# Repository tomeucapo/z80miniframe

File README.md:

# Z80MiniFrame

Z80MiniFrame is a Z80-based microcomputer project. This repository contains its firmware source, hardware schematics and previously built firmware images.

## Hardware

The design includes:

- Z80 CPU
- 32 KiB ROM/EEPROM and 32 KiB RAM
- TMS9918 video display processor (VDP)
- AY-3-8910 programmable sound generator (PSG)
- Serial console
- PPI-based I/O and a keyboard interface

## Required tools
This project uses the ZMAC Z80 Macro assembler and LD80 linker from
http://48k.ca/zmac.html, as well as CMake.

## Build software
```
cmake -S . -B build
cmake --build build
```

This produces `build/bin/firmware.hex`. To program an EPROM, install `epromng`
and run `cmake --build build --target burn`.

The firmware system and EPROM programming settings can be changed at configure
time, for example with `-DFIRMWARE_SYSTEM=Z80AIO`,
`-DEPROM_MEMTYPE=27256`, and `-DEPROM_COM_PORT=COM6`.
The firmware build is configured for the `Z80AIO` target. In that configuration it also initializes the 8253 PIT. The source contains conditional code for other hardware configurations.

## Firmware

The firmware provides:

- A Z80 BASIC interpreter with VDP-aware console and graphics support
- A serial monitor for memory inspection, Intel HEX reception, execution at an address and keyboard testing
- VDP, PSG, keyboard, serial, cassette, PPI and PIT routines
- CompactFlash IDE PIO routines for 512-byte LBA28 sector reads and writes
- Interrupt-mode 2 support and firmware service routines at `RST $20`

The CompactFlash routines use the `$A0-$A7` I/O ports. Call `CF_INIT` before
transfers, then set the four-byte little-endian `CF_LBA` and two-byte
little-endian `CF_BUFFER` values and call `CF_READ_SECTOR` or
`CF_WRITE_SECTOR`. These routines provide raw sector access; they do not
implement a filesystem.

The FAT32 support validates a FAT32 superfloppy or a primary MBR partition
(`0x0B`/`0x0C`/`0x1B`/`0x1C`) and lists its root directory in BASIC with `FILES`. The BASIC
statement invokes the directory routine through the firmware `RST $20`
service dispatcher. Names are displayed in 8.3 format; file read/write
operations are not implemented yet. Monitor command `F` initializes the CF
and mounts the volume. In BASIC, enter `FILES` to initialize, mount and list
the root directory.

At startup, the monitor offers these commands:

| Key | Function |
| --- | --- |
| `B` | Start BASIC |
| `M` | Dump memory |
| `R` | Receive Intel HEX records |
| `G` | Jump to an address |
| `T` | Run the keyboard test |
| `C` | Initialize the CompactFlash card |
| `F` | Initialize the CF and mount a FAT32 volume |
| `L` | Initialize the CF and list the FAT32 root directory |
| `?` | Show help |

Monitor command `R` receives Intel HEX over the UART. It validates each
record checksum, accepts data, EOF, extended-segment and extended-linear
records within the 16-bit Z80 address space, and ignores start-address
records. Data is written only to free RAM (`TEMPSTACK+1` through `$FDFF` in
the current memory map); the upper 512 bytes are reserved for the FAT32
sector buffer.

## Repository layout

| Path | Contents |
| --- | --- |
| `source/` | Assembly source, includes, Makefile and tests |
| `source/include/` | Hardware and firmware definitions |
| `source/tests/` | Assembly and BASIC test programs |
| `source/bin/` | Build output (`firmware.hex`, linker symbols and intermediate files) |
| `firmware/` | Checked-in firmware images from earlier releases |
| `schematics/` | Hardware schematics, PCB files and component libraries |

## Programming the ROM

The Makefile has a `burn` target that invokes `epromng`. Its defaults are `MEMTYPE=27256` and `COMEPROM=COM6`; change these in `source/Makefile` to match your programmer and port before using the target. You can also program `source/bin/firmware.hex` with a compatible programmer configured for the ROM fitted to your board.

## Hardware documentation

PDF schematics are available in `schematics/`, including `CPU_IO_Board.pdf`, `VDP.pdf`, `PSG.pdf` and `SIO_PIO.pdf`. The KiCad project for the Z80 All-in-One board is in `schematics/Z80Allinone/Z80AllInOne/`.

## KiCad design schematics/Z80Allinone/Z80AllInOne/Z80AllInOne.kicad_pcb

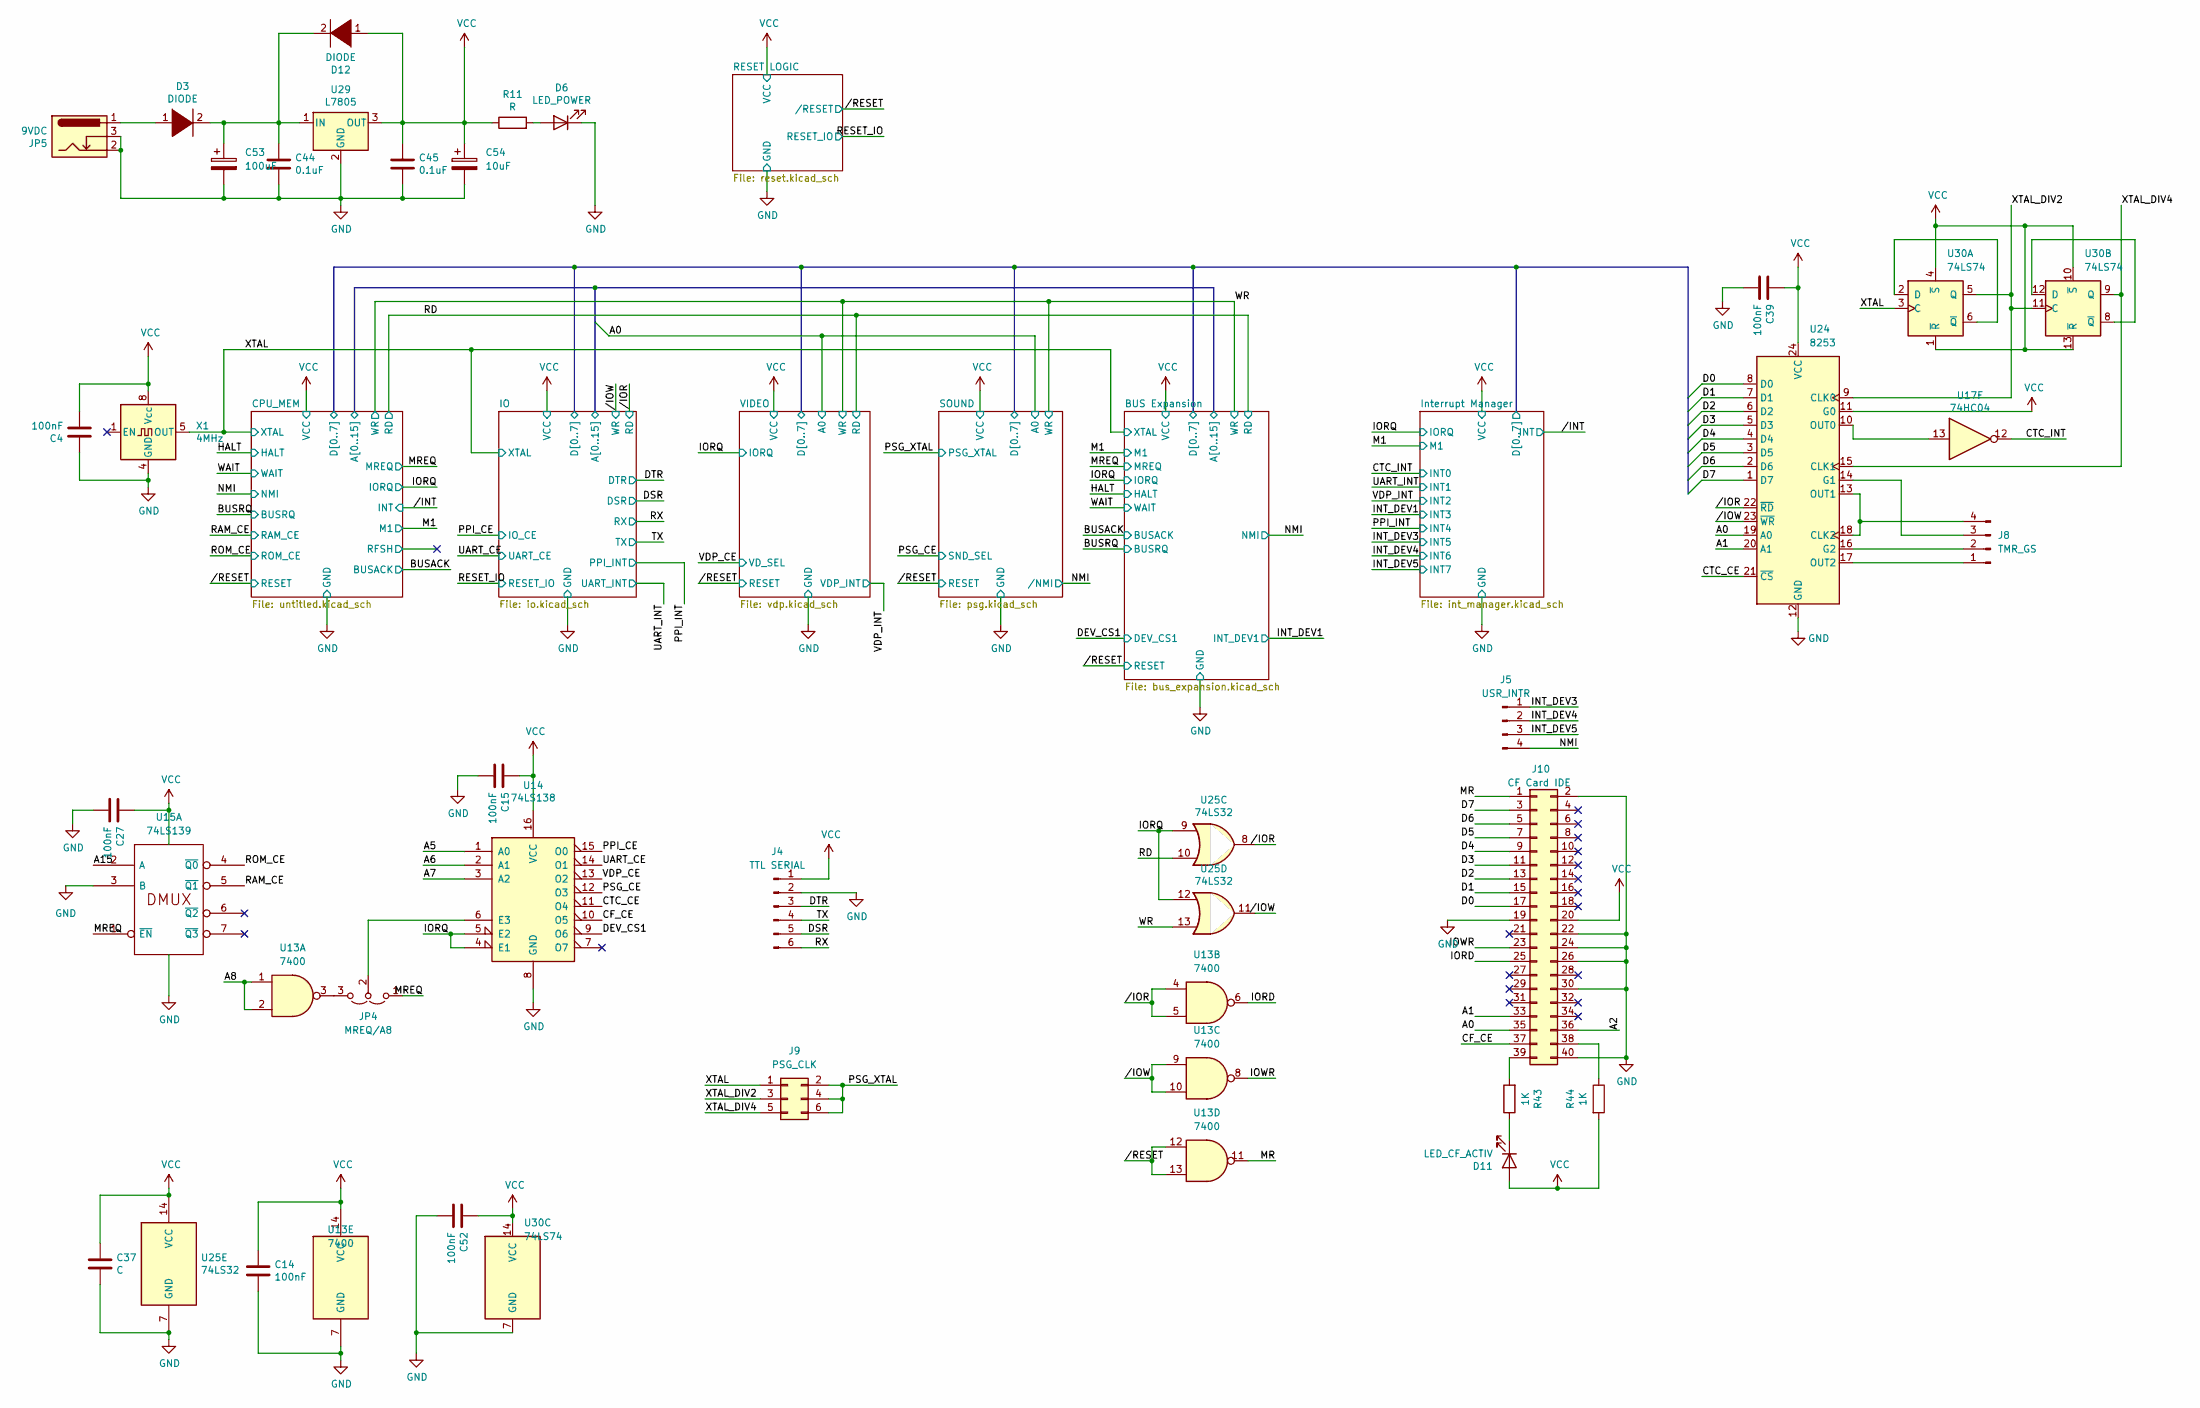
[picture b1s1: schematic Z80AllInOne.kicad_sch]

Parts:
C4, C14, C15, C27, C39, C52: 100nF; C_Disc_D7.0mm_W2.5mm_P5.00mm
C37: C; C_Disc_D7.0mm_W2.5mm_P5.00mm
C44, C45: 0.1uF; C_Radial_D6.3mm_H5.0mm_P2.50mm
C53: 100uF; CP_Radial_D8.0mm_P3.80mm
C54: 10uF; CP_Radial_D8.0mm_P3.80mm
D3, D12: DIODE; D_A-405_P7.62mm_Horizontal
D6: LED_POWER; LED_D3.0mm
D11: LED_CF_ACTIV; LED_D3.0mm
J4: TTL SERIAL; PinHeader_1x06_P2.54mm_Vertical
J5: USR_INTR; PinHeader_1x04_P2.54mm_Vertical
J8: TMR_GS; PinHeader_1x04_P2.54mm_Vertical
J9: PSG_CLK; PinHeader_2x03_P2.54mm_Vertical
J10: CF Card IDE; IDC-Header_2x20_P2.54mm_Vertical
JP4: MREQ/A8; PinHeader_1x03_P2.54mm_Vertical
JP5: 9VDC; BarrelJack_Wuerth_6941xx301002
R11: R; R_Axial_DIN0207_L6.3mm_D2.5mm_P10.16mm_Horizontal
R43, R44: 1K; R_Axial_DIN0207_L6.3mm_D2.5mm_P10.16mm_Horizontal
U13: 7400; DIP-14_W7.62mm_LongPads
U14: 74LS138; DIP-16_W7.62mm_LongPads
U15: 74LS139; DIP-16_W7.62mm_Socket
U17: 74HC04; DIP-14_W7.62mm_Socket_LongPads
U24: 8253; DIP-24_W15.24mm
U25: 74LS32; DIP-14_W7.62mm_LongPads
U29: L7805; TO-220-3_Horizontal_TabDown
U30: 74LS74; DIP-14_W7.62mm_LongPads
X1: 4MHz; Oscillator_DIP-8

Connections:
/BUS Expansion/D0: J10.17, U24.8 (D0); also elsewhere on the board
/BUS Expansion/D1: J10.15, U24.7 (D1); also elsewhere on the board
/BUS Expansion/D2: J10.13, U24.6 (D2); also elsewhere on the board
/BUS Expansion/D3: J10.11, U24.5 (D3); also elsewhere on the board
/BUS Expansion/D4: J10.9, U24.4 (D4); also elsewhere on the board
/BUS Expansion/D5: J10.7, U24.3 (D5); also elsewhere on the board
/BUS Expansion/D6: J10.5, U24.2 (D6); also elsewhere on the board
/BUS Expansion/D7: J10.3, U24.1 (D7); also elsewhere on the board
/CF_CE: J10.37, U14.10 (O5)
/CTC_CE: U14.11 (O4), U24.21 (~CS)
/CTC_INT: U17.12; also elsewhere on the board
/DEV_CS1: U14.9 (O6); also elsewhere on the board
/DSR: J4.5; also elsewhere on the board
/DTR: J4.3; also elsewhere on the board
/INT_DEV3: J5.1; also elsewhere on the board
/INT_DEV4: J5.2; also elsewhere on the board
/INT_DEV5: J5.3; also elsewhere on the board
/IO/A0: J10.35, U24.19 (A0); also elsewhere on the board
/IO/A1: J10.33, U24.20 (A1); also elsewhere on the board
/IO/A2: J10.36; also elsewhere on the board
/IO/A5: U14.1 (A0); also elsewhere on the board
/IO/A6: U14.2 (A1); also elsewhere on the board
/IO/A7: U14.3 (A2); also elsewhere on the board
/IO/A8: U13.1, U13.2; also elsewhere on the board
/IO/A15: U15.2 (A); also elsewhere on the board
/IORD: J10.25, U13.6
/IORQ: U14.4 (E1), U14.5 (E2), U25.9, U25.12; also elsewhere on the board
/IOWR: J10.23, U13.8
/MR: J10.1, U13.11
/MREQ: JP4.1 (A), U15.1 (~EN); also elsewhere on the board
/NMI: J5.4; also elsewhere on the board
/PPI_CE: U14.15 (O0); also elsewhere on the board
/PSG_CE: U14.12 (O3); also elsewhere on the board
/PSG_XTAL: J9.2, J9.4, J9.6; also elsewhere on the board
/RAM_CE: U15.5 (~Q1); also elsewhere on the board
/RD: U25.10; also elsewhere on the board
/ROM_CE: U15.4 (~Q0); also elsewhere on the board
/RX: J4.6; also elsewhere on the board
/TX: J4.4; also elsewhere on the board
/UART_CE: U14.14 (O1); also elsewhere on the board
/VDP_CE: U14.13 (O2); also elsewhere on the board
/WR: U25.13; also elsewhere on the board
/XTAL: J9.1, U30.3 (C), X1.5 (OUT); also elsewhere on the board
/XTAL_DIV2: J9.3, U24.9 (CLK0), U30.5 (Q), U30.11 (C)
/XTAL_DIV4: J9.5, U24.15 (CLK1), U30.9 (Q)
//IOR: U13.4, U13.5, U24.22 (~RD), U25.8; also elsewhere on the board
//IOW: U13.9, U13.10, U24.23 (~WR), U25.11; also elsewhere on the board
//RESET: U13.12, U13.13; also elsewhere on the board
GND: C4.1, C14.2, C15.2, C27.2, C37.1, C39.2, C44.2, C45.2, C52.2, C53.2, C54.2, D6.1 (K), J4.2, J10.2, J10.19, J10.22, J10.24, J10.26, J10.30, J10.40, JP5.2, JP5.3, U13.7 (GND), U14.8 (GND), U15.3 (B), U15.8 (GND), U24.12 (GND), U25.7 (GND), U29.2 (GND), U30.7 (GND), X1.4 (GND); also elsewhere on the board
unnamed: D3.1 (K), JP5.1
unnamed: D6.2 (A), R11.2
unnamed: D11.1 (K), R43.1
unnamed: C44.1, C53.1, D3.2 (A), D12.2 (A), U29.1 (IN)
unnamed: J8.1, U24.17 (OUT2)
unnamed: J8.2, U24.16 (G2)
unnamed: J8.3, U24.14 (G1)
unnamed: J8.4, U24.13 (OUT1), U24.18 (CLK2)
unnamed: J10.38, R44.1
unnamed: J10.39, R43.2
unnamed: JP4.3 (B), U13.3
unnamed: JP4.2 (C), U14.6 (E3)
unnamed: U17.13, U24.10 (OUT0)
unnamed: U30.2 (D), U30.6 (~Q)
unnamed: U30.8 (~Q), U30.12 (D)
VCC: C4.2, C14.1, C15.1, C27.1, C37.2, C39.1, C45.1, C52.1, C54.1, D11.2 (A), D12.1 (K), J4.1, J10.20, R11.1, R44.2, U13.14 (VCC), U14.16 (VCC), U15.16 (VCC), U24.11 (G0), U24.24 (VCC), U25.14 (VCC), U29.3 (OUT), U30.1 (~R), U30.4 (~S), U30.10 (~S), U30.13 (~R), U30.14 (VCC), X1.8 (Vcc); also elsewhere on the board

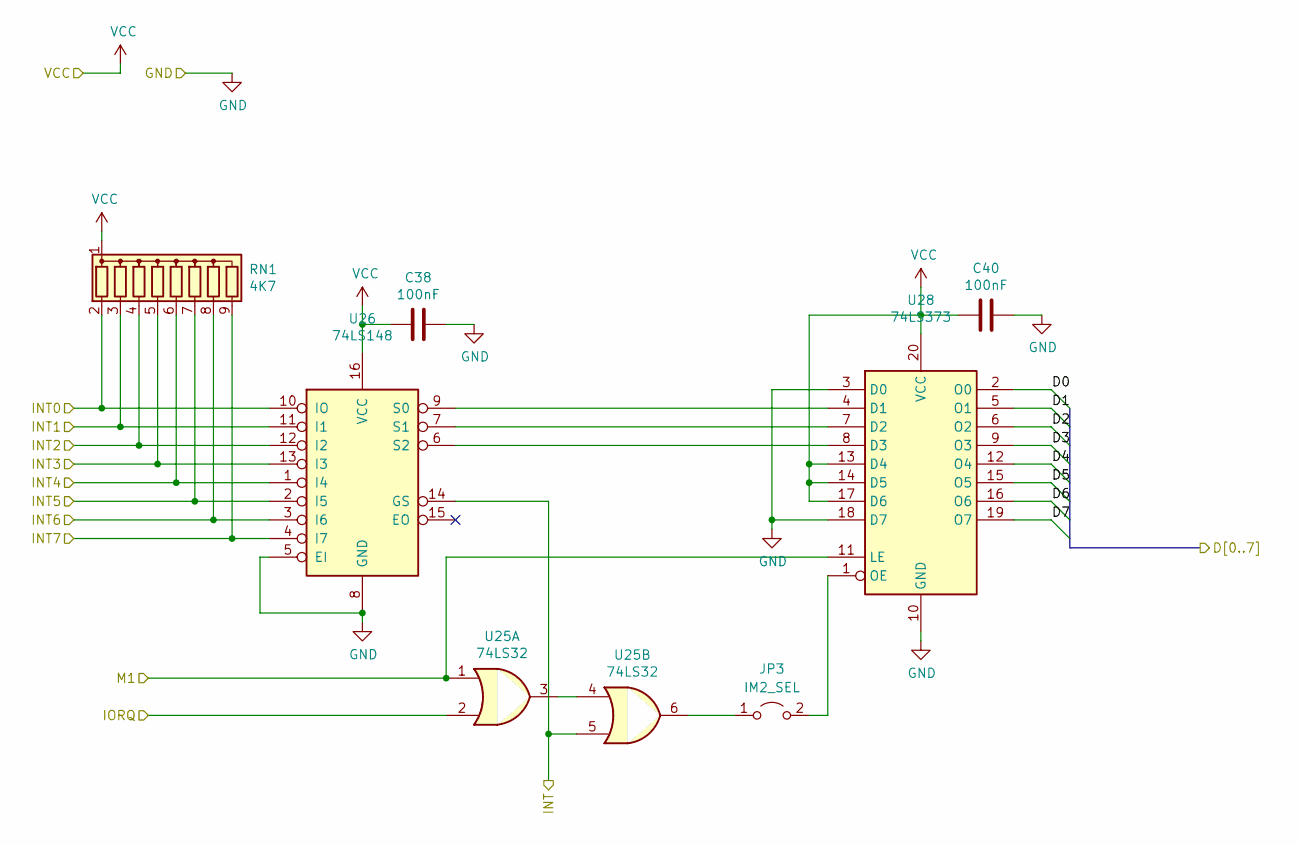
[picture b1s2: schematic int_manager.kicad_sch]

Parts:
C38, C40: 100nF; C_Disc_D7.0mm_W2.5mm_P5.00mm
JP3: IM2_SEL; PinHeader_1x02_P2.54mm_Vertical
RN1: 4K7; R_Array_SIP9
U25: 74LS32; DIP-14_W7.62mm_LongPads
U26: 74LS148; DIP-16_W7.62mm_LongPads
U28: 74LS373; DIP-20_W7.62mm_LongPads

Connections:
/BUS Expansion/D0: U28.2 (O0); also elsewhere on the board
/BUS Expansion/D1: U28.5 (O1); also elsewhere on the board
/BUS Expansion/D2: U28.6 (O2); also elsewhere on the board
/BUS Expansion/D3: U28.9 (O3); also elsewhere on the board
/BUS Expansion/D4: U28.12 (O4); also elsewhere on the board
/BUS Expansion/D5: U28.15 (O5); also elsewhere on the board
/BUS Expansion/D6: U28.16 (O6); also elsewhere on the board
/BUS Expansion/D7: U28.19 (O7); also elsewhere on the board
/CTC_INT: RN1.2 (R1), U26.10 (IO); also elsewhere on the board
/INT_DEV1: RN1.5 (R4), U26.13 (I3); also elsewhere on the board
/INT_DEV3: RN1.7 (R6), U26.2 (I5); also elsewhere on the board
/INT_DEV4: RN1.8 (R7), U26.3 (I6); also elsewhere on the board
/INT_DEV5: RN1.9 (R8), U26.4 (I7); also elsewhere on the board
/IORQ: U25.2; also elsewhere on the board
/M1: U25.1, U28.11 (LE); also elsewhere on the board
/PPI_INT: RN1.6 (R5), U26.1 (I4); also elsewhere on the board
/UART_INT: RN1.3 (R2), U26.11 (I1); also elsewhere on the board
/VDP_INT: RN1.4 (R3), U26.12 (I2); also elsewhere on the board
//INT: U25.5, U26.14 (GS); also elsewhere on the board
GND: C38.2, C40.2, U26.5 (EI), U26.8 (GND), U28.3 (D0), U28.10 (GND), U28.18 (D7); also elsewhere on the board
unnamed: JP3.1 (A), U25.6
unnamed: JP3.2 (B), U28.1 (OE)
unnamed: U25.3, U25.4
unnamed: U26.9 (S0), U28.4 (D1)
unnamed: U26.7 (S1), U28.7 (D2)
unnamed: U26.6 (S2), U28.8 (D3)
VCC: C38.1, C40.1, RN1.1 (common), U26.16 (VCC), U28.13 (D4), U28.14 (D5), U28.17 (D6), U28.20 (VCC); also elsewhere on the board

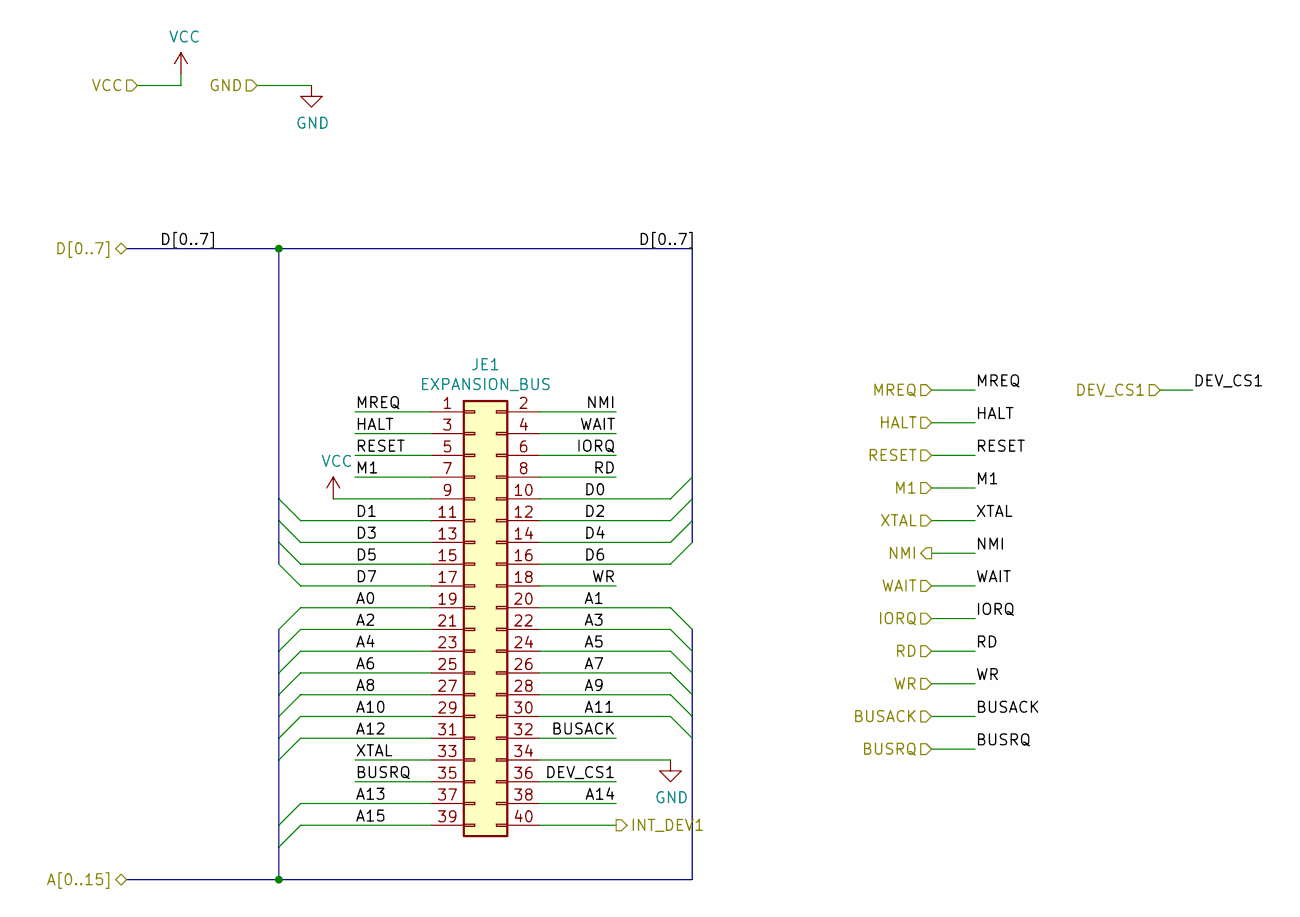
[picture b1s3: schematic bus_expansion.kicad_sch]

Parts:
JE1: EXPANSION_BUS; EdgeConector_40pin

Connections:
/BUS Expansion/D0: JE1.10; also elsewhere on the board
/BUS Expansion/D1: JE1.11; also elsewhere on the board
/BUS Expansion/D2: JE1.12; also elsewhere on the board
/BUS Expansion/D3: JE1.13; also elsewhere on the board
/BUS Expansion/D4: JE1.14; also elsewhere on the board
/BUS Expansion/D5: JE1.15; also elsewhere on the board
/BUS Expansion/D6: JE1.16; also elsewhere on the board
/BUS Expansion/D7: JE1.17; also elsewhere on the board
/BUSACK: JE1.32; also elsewhere on the board
/BUSRQ: JE1.35; also elsewhere on the board
/DEV_CS1: JE1.36; also elsewhere on the board
/HALT: JE1.3; also elsewhere on the board
/INT_DEV1: JE1.40; also elsewhere on the board
/IO/A0: JE1.19; also elsewhere on the board
/IO/A1: JE1.20; also elsewhere on the board
/IO/A2: JE1.21; also elsewhere on the board
/IO/A3: JE1.22; also elsewhere on the board
/IO/A4: JE1.23; also elsewhere on the board
/IO/A5: JE1.24; also elsewhere on the board
/IO/A6: JE1.25; also elsewhere on the board
/IO/A7: JE1.26; also elsewhere on the board
/IO/A8: JE1.27; also elsewhere on the board
/IO/A9: JE1.28; also elsewhere on the board
/IO/A10: JE1.29; also elsewhere on the board
/IO/A11: JE1.30; also elsewhere on the board
/IO/A12: JE1.31; also elsewhere on the board
/IO/A13: JE1.37; also elsewhere on the board
/IO/A14: JE1.38; also elsewhere on the board
/IO/A15: JE1.39; also elsewhere on the board
/IORQ: JE1.6; also elsewhere on the board
/M1: JE1.7; also elsewhere on the board
/MREQ: JE1.1; also elsewhere on the board
/NMI: JE1.2; also elsewhere on the board
/RD: JE1.8; also elsewhere on the board
/WAIT: JE1.4; also elsewhere on the board
/WR: JE1.18; also elsewhere on the board
/XTAL: JE1.33; also elsewhere on the board
//RESET: JE1.5; also elsewhere on the board
GND: JE1.34; also elsewhere on the board
VCC: JE1.9; also elsewhere on the board

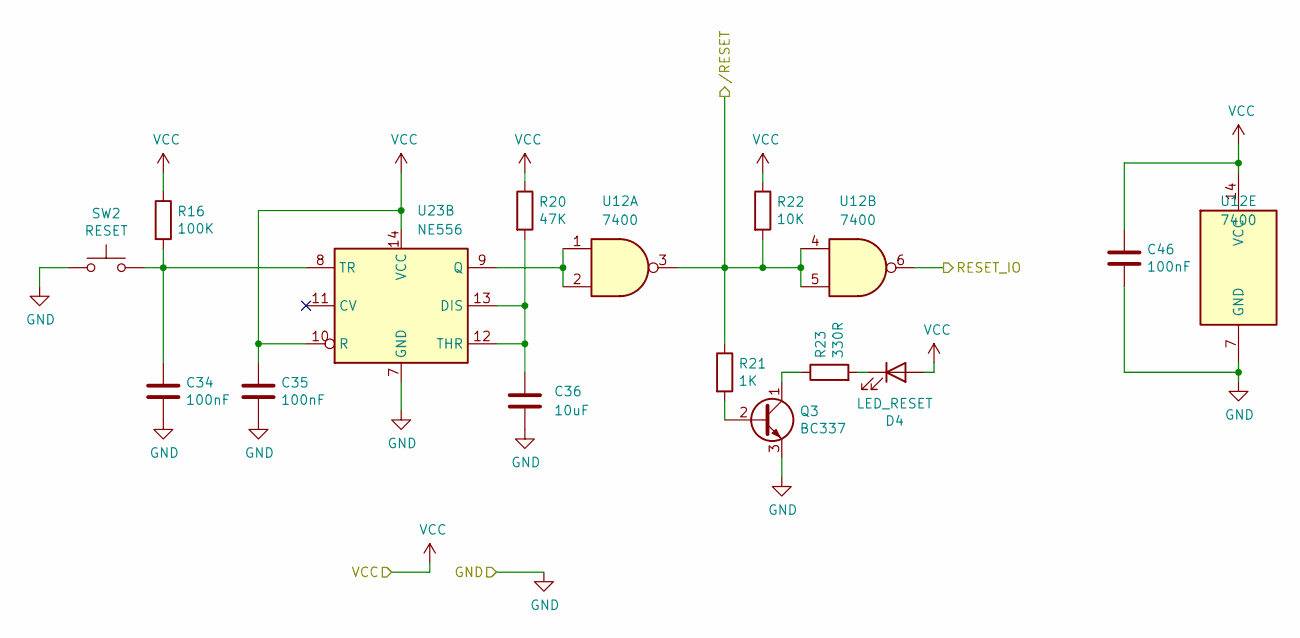
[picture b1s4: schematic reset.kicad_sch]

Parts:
C34, C35, C46: 100nF; C_Disc_D7.0mm_W2.5mm_P5.00mm
C36: 10uF; CP_Radial_D5.0mm_P2.50mm
D4: LED_RESET; LED_D3.0mm
Q3: BC337; TO-92_Inline
R16: 100K; R_Axial_DIN0207_L6.3mm_D2.5mm_P7.62mm_Horizontal
R20: 47K; R_Axial_DIN0207_L6.3mm_D2.5mm_P7.62mm_Horizontal
R21: 1K; R_Axial_DIN0207_L6.3mm_D2.5mm_P7.62mm_Horizontal
R22: 10K; R_Axial_DIN0207_L6.3mm_D2.5mm_P7.62mm_Horizontal
R23: 330R; R_Axial_DIN0207_L6.3mm_D2.5mm_P7.62mm_Horizontal
SW2: RESET; SW_PUSH_6mm_H5mm
U12: 7400; DIP-14_W7.62mm_LongPads
U23: NE556; DIP-14_W7.62mm_LongPads

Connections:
/RESET_IO: U12.6; also elsewhere on the board
//RESET: R21.1, R22.2, U12.3, U12.4, U12.5; also elsewhere on the board
GND: C34.2, C35.2, C36.2, C46.2, Q3.3 (E), SW2.1, U12.7 (GND), U23.7 (GND); also elsewhere on the board
unnamed: D4.1 (K), R23.2
unnamed: Q3.2 (B), R21.2
unnamed: Q3.1 (C), R23.1
unnamed: C36.1, R20.2, U23.12 (THR), U23.13 (DIS)
unnamed: U12.1, U12.2, U23.9 (Q)
unnamed: C34.1, R16.2, SW2.2, U23.8 (TR)
VCC: C35.1, C46.1, D4.2 (A), R16.1, R20.1, R22.1, U12.14 (VCC), U23.10 (R), U23.14 (VCC); also elsewhere on the board

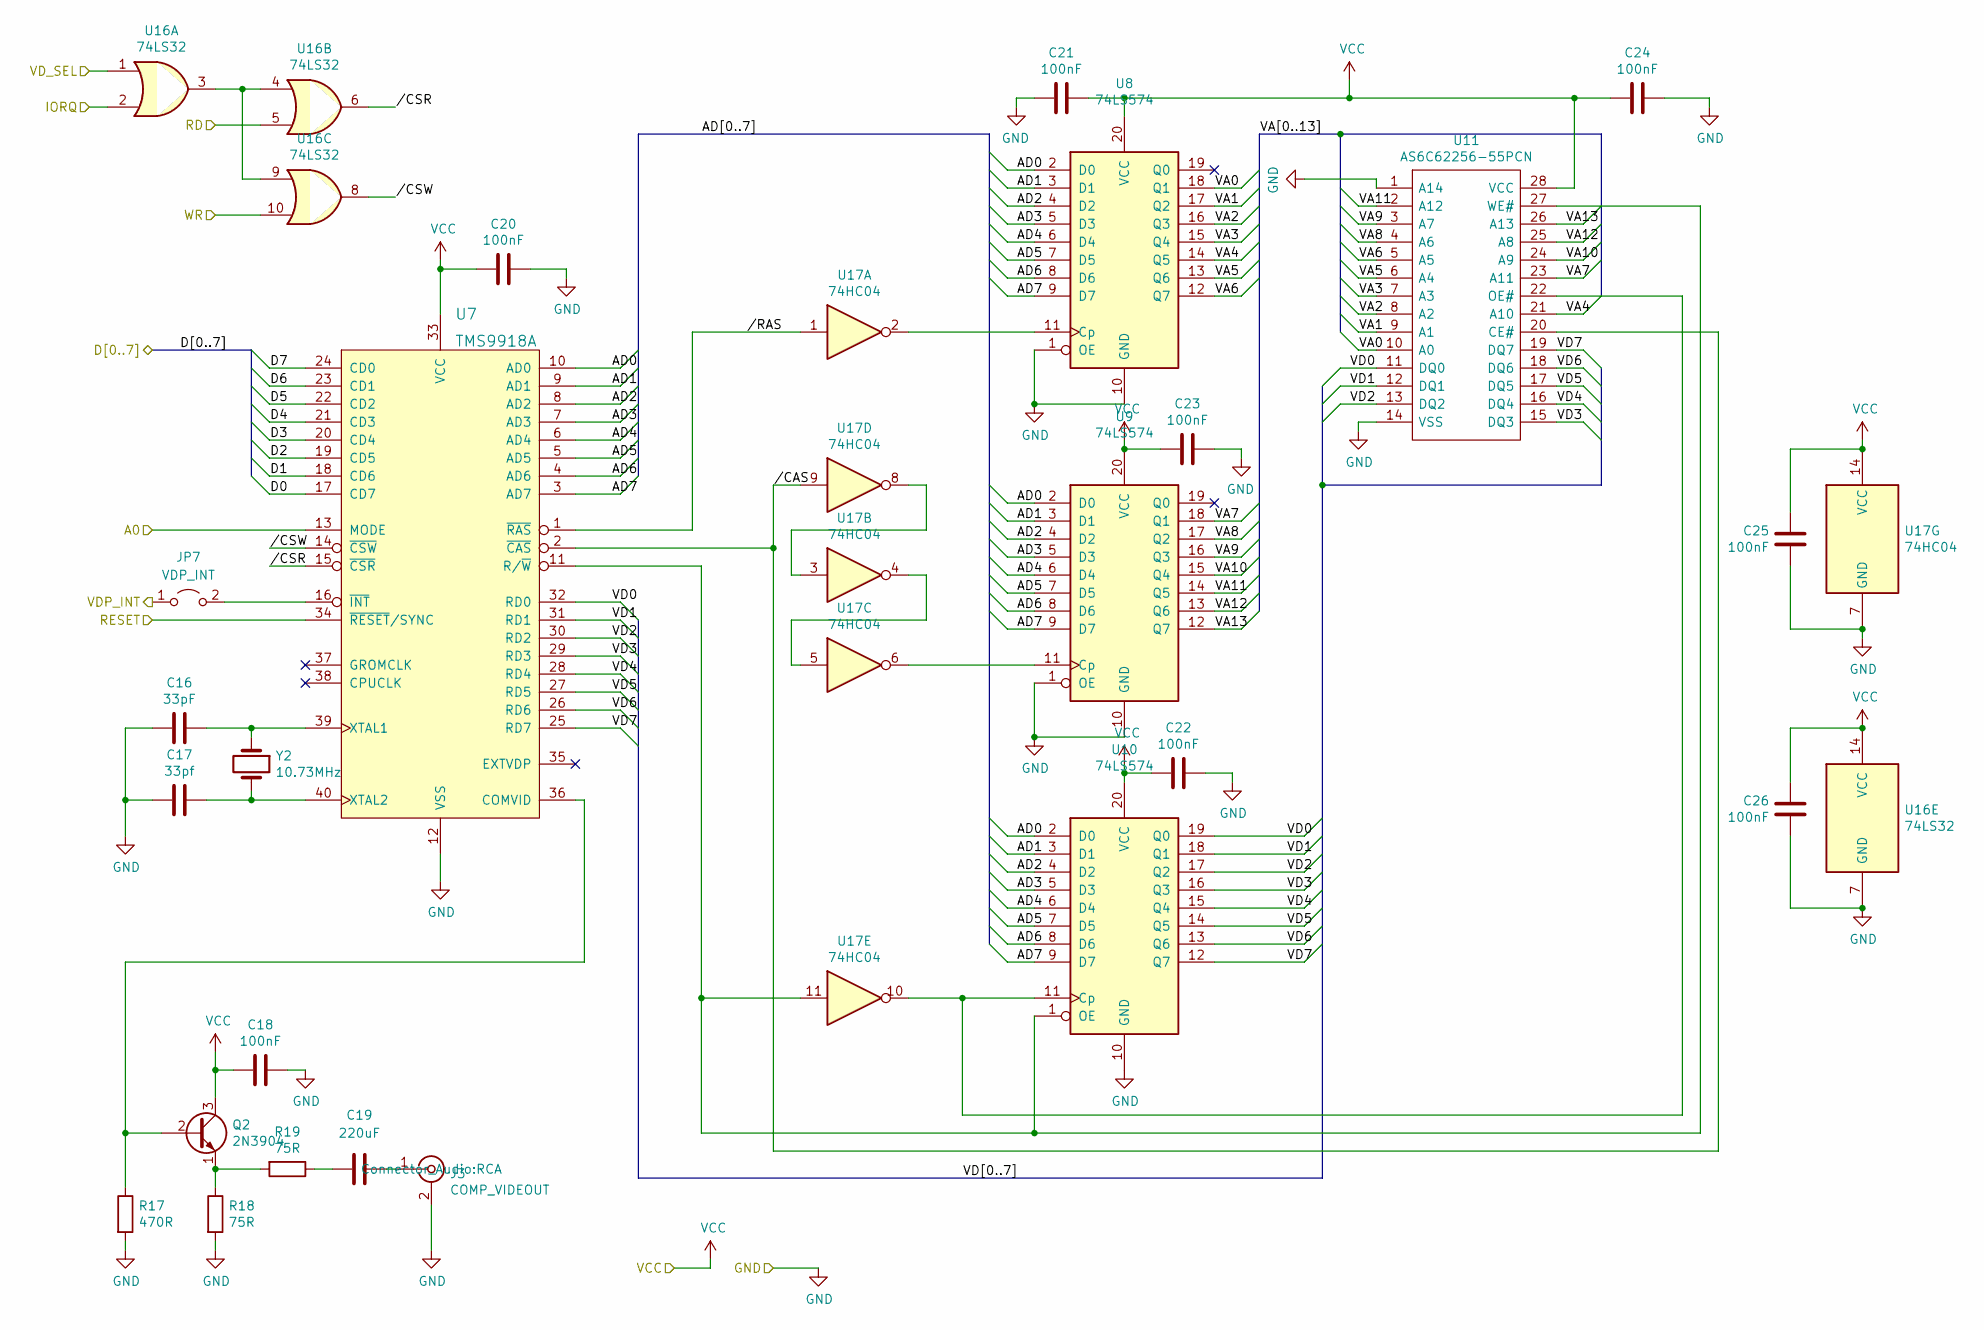
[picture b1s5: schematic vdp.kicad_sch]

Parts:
C16: 33pF; C_Disc_D7.0mm_W2.5mm_P5.00mm
C17: 33pf; C_Disc_D7.0mm_W2.5mm_P5.00mm
C18, C20, C21, C22, C23, C24, C25, C26: 100nF; C_Disc_D7.0mm_W2.5mm_P5.00mm
C19: 220uF; CP_Radial_Tantal_D6.0mm_P2.50mm
J3: COMP_VIDEOUT; RCA
JP7: VDP_INT; PinHeader_1x02_P2.54mm_Vertical
Q2: 2N3904; TO-92_Inline
R17: 470R; R_Axial_DIN0207_L6.3mm_D2.5mm_P10.16mm_Horizontal
R18, R19: 75R; R_Axial_DIN0207_L6.3mm_D2.5mm_P10.16mm_Horizontal
U7: TMS9918A; DIP-40_W15.24mm_LongPads
U8, U9, U10: 74LS574; DIP-20_W7.62mm_Socket_LongPads
U11: AS6C62256-55PCN; DIP-28_W15.24mm_LongPads; Manufacturer_Part_Number AS6C62256-55PCN; Mouser Part Number 913-AS6C62256-55PCN
U16: 74LS32; DIP-14_W7.62mm_LongPads
U17: 74HC04; DIP-14_W7.62mm_Socket_LongPads
Y2: 10.73MHz; Crystal_HC18-U_Vertical

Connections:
/BUS Expansion/D0: U7.17 (CD7); also elsewhere on the board
/BUS Expansion/D1: U7.18 (CD6); also elsewhere on the board
/BUS Expansion/D2: U7.19 (CD5); also elsewhere on the board
/BUS Expansion/D3: U7.20 (CD4); also elsewhere on the board
/BUS Expansion/D4: U7.21 (CD3); also elsewhere on the board
/BUS Expansion/D5: U7.22 (CD2); also elsewhere on the board
/BUS Expansion/D6: U7.23 (CD1); also elsewhere on the board
/BUS Expansion/D7: U7.24 (CD0); also elsewhere on the board
/IO/A0: U7.13 (MODE); also elsewhere on the board
/IORQ: U16.2; also elsewhere on the board
/RD: U16.5; also elsewhere on the board
/VDP_CE: U16.1; also elsewhere on the board
/VDP_INT: JP7.1 (A); also elsewhere on the board
/VIDEO/AD0: U7.10 (AD0), U8.2 (D0), U9.2 (D0), U10.2 (D0)
/VIDEO/AD1: U7.9 (AD1), U8.3 (D1), U9.3 (D1), U10.3 (D1)
/VIDEO/AD2: U7.8 (AD2), U8.4 (D2), U9.4 (D2), U10.4 (D2)
/VIDEO/AD3: U7.7 (AD3), U8.5 (D3), U9.5 (D3), U10.5 (D3)
/VIDEO/AD4: U7.6 (AD4), U8.6 (D4), U9.6 (D4), U10.6 (D4)
/VIDEO/AD5: U7.5 (AD5), U8.7 (D5), U9.7 (D5), U10.7 (D5)
/VIDEO/AD6: U7.4 (AD6), U8.8 (D6), U9.8 (D6), U10.8 (D6)
/VIDEO/AD7: U7.3 (AD7), U8.9 (D7), U9.9 (D7), U10.9 (D7)
/VIDEO/VA0: U8.18 (Q1), U11.10 (A0)
/VIDEO/VA1: U8.17 (Q2), U11.9 (A1)
/VIDEO/VA2: U8.16 (Q3), U11.8 (A2)
/VIDEO/VA3: U8.15 (Q4), U11.7 (A3)
/VIDEO/VA4: U8.14 (Q5), U11.21 (A10)
/VIDEO/VA5: U8.13 (Q6), U11.6 (A4)
/VIDEO/VA6: U8.12 (Q7), U11.5 (A5)
/VIDEO/VA7: U9.18 (Q1), U11.23 (A11)
/VIDEO/VA8: U9.17 (Q2), U11.4 (A6)
/VIDEO/VA9: U9.16 (Q3), U11.3 (A7)
/VIDEO/VA10: U9.15 (Q4), U11.24 (A9)
/VIDEO/VA11: U9.14 (Q5), U11.2 (A12)
/VIDEO/VA12: U9.13 (Q6), U11.25 (A8)
/VIDEO/VA13: U9.12 (Q7), U11.26 (A13)
/VIDEO/VD0: U7.32 (RD0), U10.19 (Q0), U11.11 (DQ0)
/VIDEO/VD1: U7.31 (RD1), U10.18 (Q1), U11.12 (DQ1)
/VIDEO/VD2: U7.30 (RD2), U10.17 (Q2), U11.13 (DQ2)
/VIDEO/VD3: U7.29 (RD3), U10.16 (Q3), U11.15 (DQ3)
/VIDEO/VD4: U7.28 (RD4), U10.15 (Q4), U11.16 (DQ4)
/VIDEO/VD5: U7.27 (RD5), U10.14 (Q5), U11.17 (DQ5)
/VIDEO/VD6: U7.26 (RD6), U10.13 (Q6), U11.18 (DQ6)
/VIDEO/VD7: U7.25 (RD7), U10.12 (Q7), U11.19 (DQ7)
/VIDEO//CAS: U7.2 (~CAS), U11.20 (CE#), U17.9
/VIDEO//CSR: U7.15 (~CSR), U16.6
/VIDEO//CSW: U7.14 (~CSW), U16.8
/VIDEO//RAS: U7.1 (~RAS), U17.1
/WR: U16.10; also elsewhere on the board
//RESET: U7.34 (~RESET/SYNC); also elsewhere on the board
GND: C16.1, C17.1, C18.1, C20.2, C21.2, C22.1, C23.1, C24.1, C25.1, C26.1, J3.2 (Ext), R17.2, R18.2, U7.12 (VSS), U8.1 (OE), U8.10 (GND), U9.1 (OE), U9.10 (GND), U10.10 (GND), U11.1 (A14), U11.14 (VSS), U16.7 (GND), U17.7 (GND); also elsewhere on the board
unnamed: C19.1, R19.1
unnamed: C19.2, J3.1 (In)
unnamed: JP7.2 (B), U7.16 (~INT)
unnamed: Q2.2 (B), R17.1, U7.36 (COMVID)
unnamed: Q2.1 (E), R18.1, R19.2
unnamed: C16.2, U7.39 (XTAL1), Y2.1
unnamed: C17.2, U7.40 (XTAL2), Y2.2
unnamed: U8.11 (Cp), U17.2
unnamed: U9.11 (Cp), U17.6
unnamed: U10.11 (Cp), U11.22 (OE#), U17.10
unnamed: U7.11 (R/~W), U10.1 (OE), U11.27 (WE#), U17.11
unnamed: U16.3, U16.4, U16.9
unnamed: U17.3, U17.8
unnamed: U17.4, U17.5
VCC: C18.2, C20.1, C21.1, C22.2, C23.2, C24.2, C25.2, C26.2, Q2.3 (C), U7.33 (VCC), U8.20 (VCC), U9.20 (VCC), U10.20 (VCC), U11.28 (VCC), U16.14 (VCC), U17.14 (VCC); also elsewhere on the board

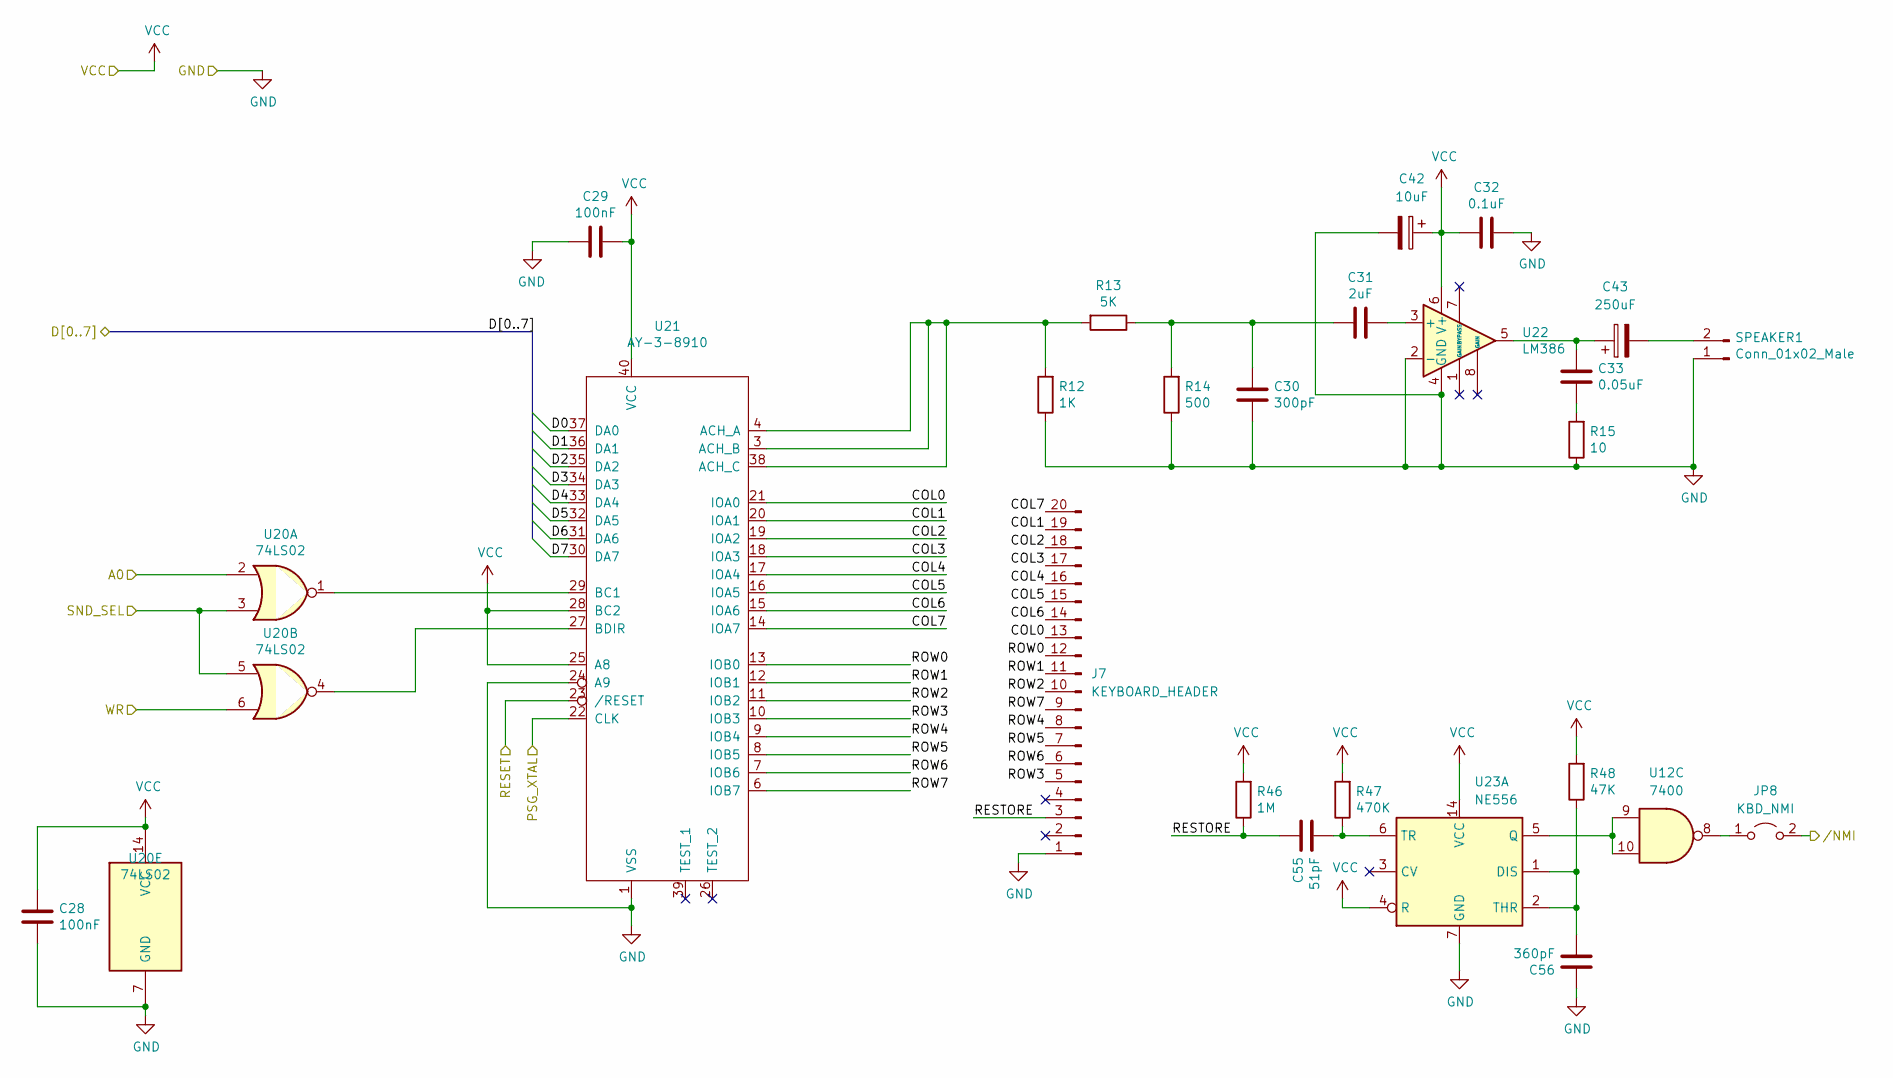
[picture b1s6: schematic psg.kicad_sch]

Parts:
C28, C29: 100nF; C_Disc_D7.0mm_W2.5mm_P5.00mm
C30: 300pF; C_Disc_D5.0mm_W2.5mm_P5.00mm
C31: 2uF; C_Disc_D5.0mm_W2.5mm_P5.00mm
C32: 0.1uF; C_Disc_D7.0mm_W2.5mm_P5.00mm
C33: 0.05uF; C_Disc_D5.0mm_W2.5mm_P5.00mm
C42: 10uF; CP_Radial_D5.0mm_P2.00mm
C43: 250uF; CP_Radial_D6.3mm_P2.50mm
C55: 51pF; C_Disc_D5.0mm_W2.5mm_P5.00mm
C56: 360pF; C_Disc_D5.0mm_W2.5mm_P5.00mm
J7: KEYBOARD_HEADER; PinHeader_1x20_P2.54mm_Vertical
JP8: KBD_NMI; PinHeader_1x02_P2.54mm_Vertical
R12: 1K; R_Axial_DIN0207_L6.3mm_D2.5mm_P10.16mm_Horizontal
R13: 5K; R_Axial_DIN0207_L6.3mm_D2.5mm_P10.16mm_Horizontal
R14: 500; R_Axial_DIN0207_L6.3mm_D2.5mm_P10.16mm_Horizontal
R15: 10; R_Axial_DIN0207_L6.3mm_D2.5mm_P10.16mm_Horizontal
R46: 1M; R_Axial_DIN0207_L6.3mm_D2.5mm_P10.16mm_Horizontal
R47: 470K; R_Axial_DIN0207_L6.3mm_D2.5mm_P10.16mm_Horizontal
R48: 47K; R_Axial_DIN0207_L6.3mm_D2.5mm_P10.16mm_Horizontal
SPEAKER1: Conn_01x02_Male; PinHeader_1x02_P2.54mm_Vertical
U12: 7400; DIP-14_W7.62mm_LongPads
U20: 74LS02; DIP-14_W7.62mm_Socket_LongPads
U21: AY-3-8910; DIP-40_W15.24mm_LongPads
U22: LM386; DIP-8_W7.62mm_LongPads
U23: NE556; DIP-14_W7.62mm_LongPads

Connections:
/BUS Expansion/D0: U21.37 (DA0); also elsewhere on the board
/BUS Expansion/D1: U21.36 (DA1); also elsewhere on the board
/BUS Expansion/D2: U21.35 (DA2); also elsewhere on the board
/BUS Expansion/D3: U21.34 (DA3); also elsewhere on the board
/BUS Expansion/D4: U21.33 (DA4); also elsewhere on the board
/BUS Expansion/D5: U21.32 (DA5); also elsewhere on the board
/BUS Expansion/D6: U21.31 (DA6); also elsewhere on the board
/BUS Expansion/D7: U21.30 (DA7); also elsewhere on the board
/IO/A0: U20.2; also elsewhere on the board
/NMI: JP8.2 (B); also elsewhere on the board
/PSG_CE: U20.3, U20.5; also elsewhere on the board
/PSG_XTAL: U21.22 (CLK); also elsewhere on the board
/SOUND/COL0: J7.13, U21.21 (IOA0)
/SOUND/COL1: J7.19, U21.20 (IOA1)
/SOUND/COL2: J7.18, U21.19 (IOA2)
/SOUND/COL3: J7.17, U21.18 (IOA3)
/SOUND/COL4: J7.16, U21.17 (IOA4)
/SOUND/COL5: J7.15, U21.16 (IOA5)
/SOUND/COL6: J7.14, U21.15 (IOA6)
/SOUND/COL7: J7.20, U21.14 (IOA7)
/SOUND/RESTORE: C55.1, J7.3, R46.1
/SOUND/ROW0: J7.12, U21.13 (IOB0)
/SOUND/ROW1: J7.11, U21.12 (IOB1)
/SOUND/ROW2: J7.10, U21.11 (IOB2)
/SOUND/ROW3: J7.5, U21.10 (IOB3)
/SOUND/ROW4: J7.8, U21.9 (IOB4)
/SOUND/ROW5: J7.7, U21.8 (IOB5)
/SOUND/ROW6: J7.6, U21.7 (IOB6)
/SOUND/ROW7: J7.9, U21.6 (IOB7)
/WR: U20.6; also elsewhere on the board
//RESET: U21.23 (/RESET); also elsewhere on the board
GND: C28.1, C29.2, C30.2, C32.2, C42.2, C56.1, J7.1, R12.1, R14.1, R15.1, SPEAKER1.1, U20.7 (GND), U21.1 (VSS), U21.24 (A9), U22.2 (-), U22.4 (GND), U23.7 (GND); also elsewhere on the board
unnamed: C30.1, C31.2, R13.1, R14.2
unnamed: C33.1, C43.1, U22.5
unnamed: C33.2, R15.2
unnamed: JP8.1 (A), U12.8
unnamed: C43.2, SPEAKER1.2
unnamed: R12.2, R13.2, U21.3 (ACH_B), U21.4 (ACH_A), U21.38 (ACH_C)
unnamed: U20.1, U21.29 (BC1)
unnamed: U20.4, U21.27 (BDIR)
unnamed: C31.1, U22.3 (+)
unnamed: C56.2, R48.1, U23.1 (DIS), U23.2 (THR)
unnamed: U12.9, U12.10, U23.5 (Q)
unnamed: C55.2, R47.1, U23.6 (TR)
VCC: C28.2, C29.1, C32.1, C42.1, R46.2, R47.2, R48.2, U20.14 (VCC), U21.25 (A8), U21.28 (BC2), U21.40 (VCC), U22.6 (V+), U23.4 (R), U23.14 (VCC); also elsewhere on the board
